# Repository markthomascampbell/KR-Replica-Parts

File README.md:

This repository aims to collect many of the various 3d stencils, Arduino sketches, code, schematics, and any other documentation on creating Knight Rider replica parts.

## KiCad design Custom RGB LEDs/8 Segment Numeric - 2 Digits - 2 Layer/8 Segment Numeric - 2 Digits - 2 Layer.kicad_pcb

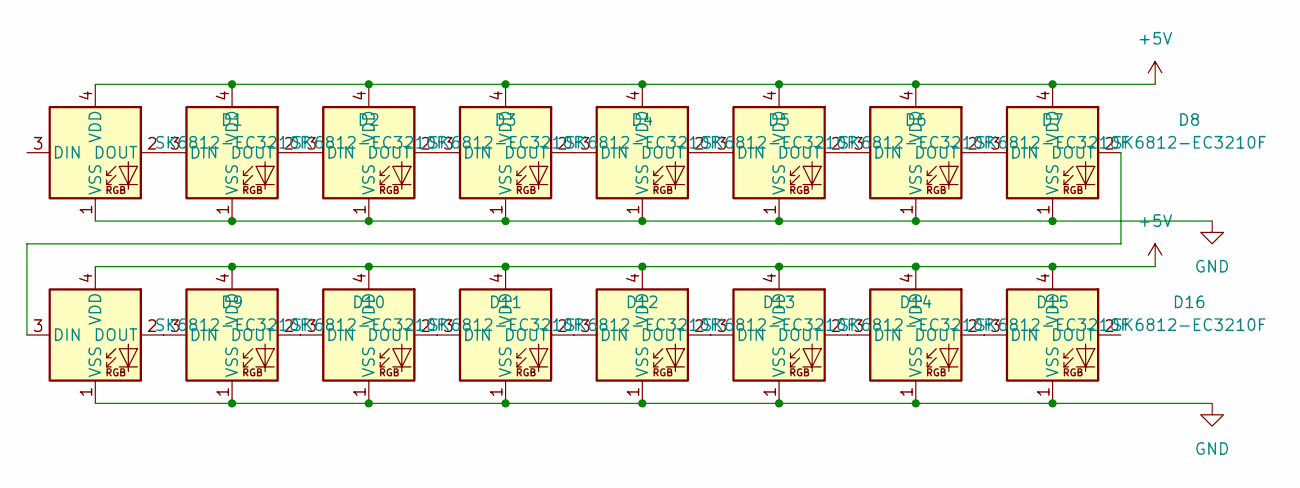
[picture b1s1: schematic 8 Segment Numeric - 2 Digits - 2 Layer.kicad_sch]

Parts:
D1, D2, D3, D4, D5, D6, D7, D8, D9, D10, D11, D12, D13, D14, D15, D16: SK6812-EC3210F

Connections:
+5V: D1.4 (VDD), D2.4 (VDD), D3.4 (VDD), D4.4 (VDD), D5.4 (VDD), D6.4 (VDD), D7.4 (VDD), D8.4 (VDD), D9.4 (VDD), D10.4 (VDD), D11.4 (VDD), D12.4 (VDD), D13.4 (VDD), D14.4 (VDD), D15.4 (VDD), D16.4 (VDD); also elsewhere on the board
GND: D1.1 (VSS), D2.1 (VSS), D3.1 (VSS), D4.1 (VSS), D5.1 (VSS), D6.1 (VSS), D7.1 (VSS), D8.1 (VSS), D9.1 (VSS), D10.1 (VSS), D11.1 (VSS), D12.1 (VSS), D13.1 (VSS), D14.1 (VSS), D15.1 (VSS), D16.1 (VSS); also elsewhere on the board
unnamed: D1.2 (DOUT), D2.3 (DIN)
unnamed: D2.2 (DOUT), D3.3 (DIN)
unnamed: D3.2 (DOUT), D4.3 (DIN)
unnamed: D4.2 (DOUT), D5.3 (DIN)
unnamed: D5.2 (DOUT), D6.3 (DIN)
unnamed: D6.2 (DOUT), D7.3 (DIN)
unnamed: D7.2 (DOUT), D8.3 (DIN)
unnamed: D8.2 (DOUT), D9.3 (DIN)
unnamed: D9.2 (DOUT), D10.3 (DIN)
unnamed: D10.2 (DOUT), D11.3 (DIN)
unnamed: D11.2 (DOUT), D12.3 (DIN)
unnamed: D12.2 (DOUT), D13.3 (DIN)
unnamed: D13.2 (DOUT), D14.3 (DIN)
unnamed: D14.2 (DOUT), D15.3 (DIN)
unnamed: D15.2 (DOUT), D16.3 (DIN)

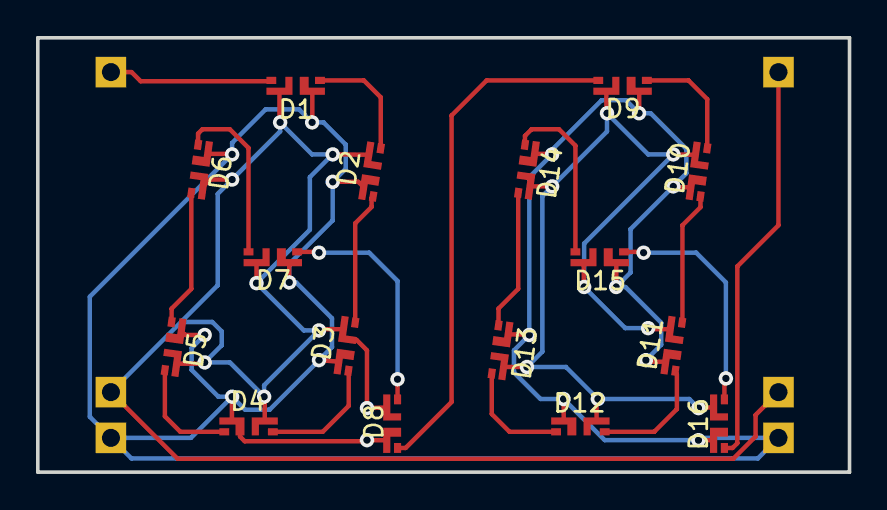
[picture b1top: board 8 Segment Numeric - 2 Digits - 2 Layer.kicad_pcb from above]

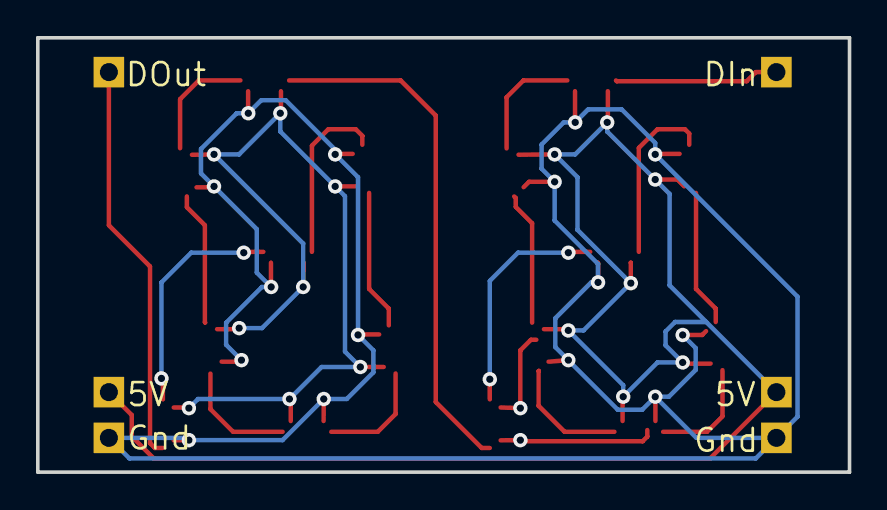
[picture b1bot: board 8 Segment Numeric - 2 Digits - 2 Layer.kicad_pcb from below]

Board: 2 copper layers, 45.1 x 24.1 mm, 18 parts (2 on the bottom side), 17 nets.

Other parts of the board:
5V: (no value)
Gnd: (no value)

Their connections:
+5V: 5V.1; also elsewhere on the board
GND: Gnd.1; also elsewhere on the board

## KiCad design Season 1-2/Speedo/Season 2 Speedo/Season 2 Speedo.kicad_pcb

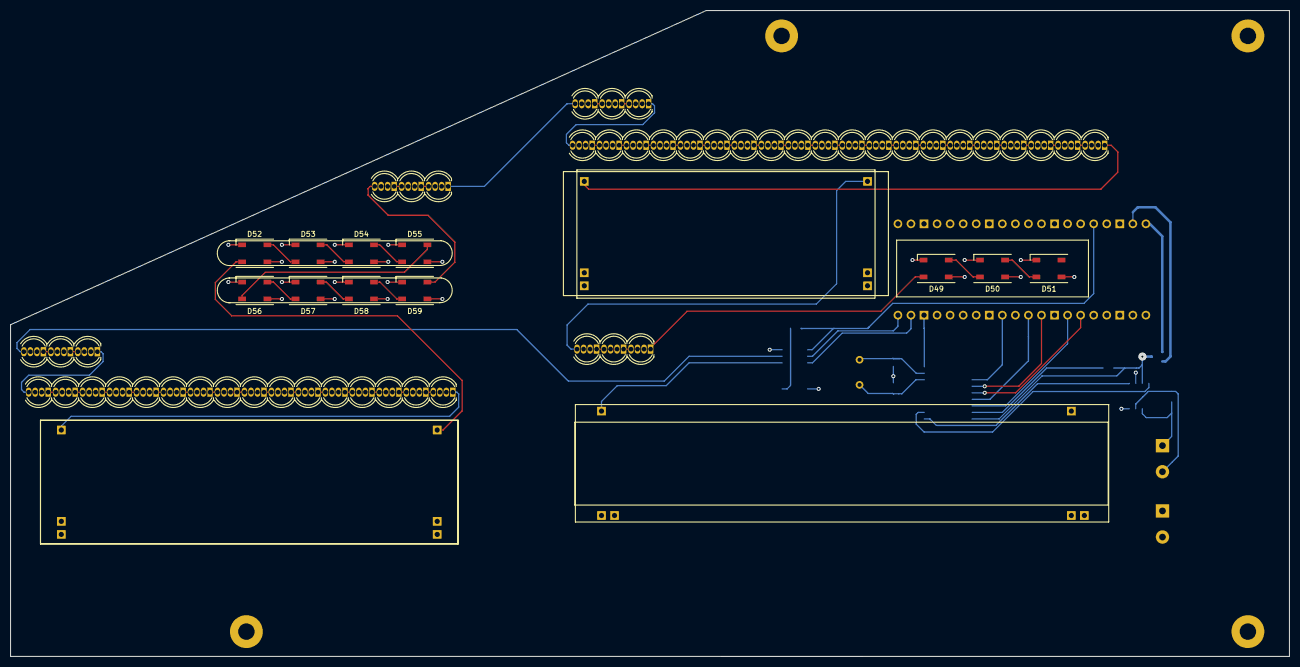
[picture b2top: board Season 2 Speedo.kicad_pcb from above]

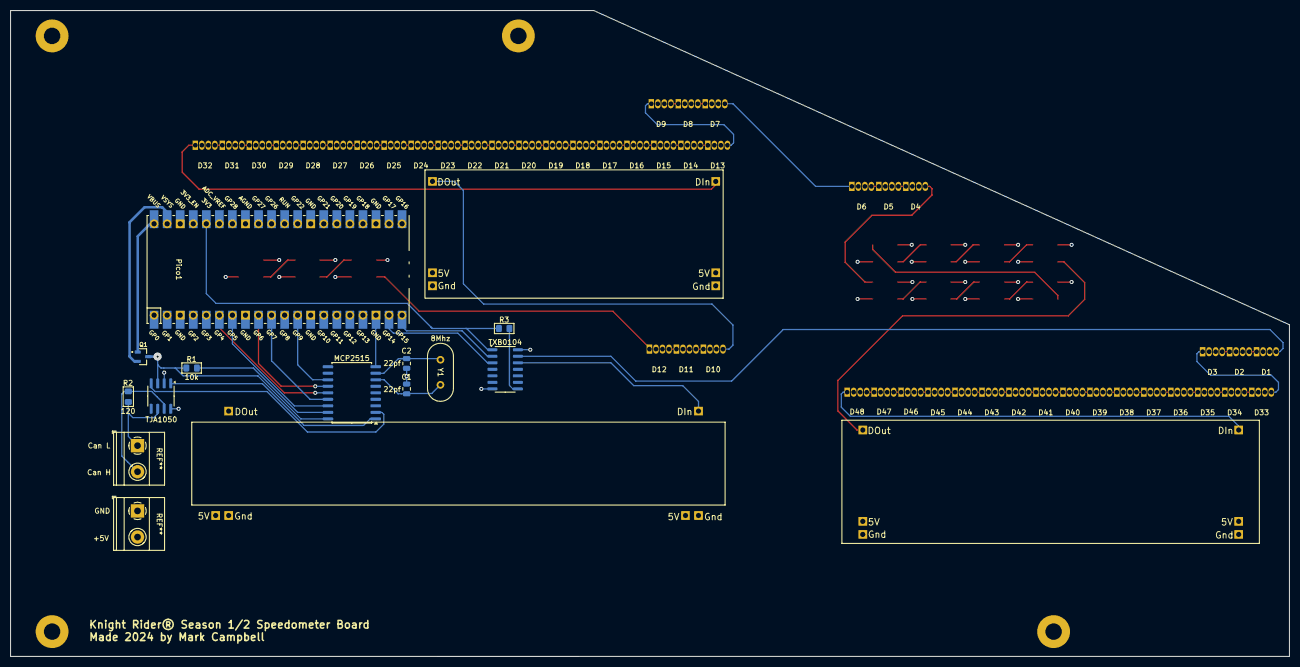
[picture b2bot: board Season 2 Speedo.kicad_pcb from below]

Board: 4 copper layers, 248.9 x 125.7 mm, 74 parts (15 on the bottom side), 77 nets.

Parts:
5V, 5V#2: (no value)
C1, C2: 22pf; C_0805_2012Metric
D1, D2, D3, D4, D5, D6, D7, D8, D9, D10, D11, D12, D13, D14, D15, D16, D17, D18, D19, D20, D21, D22, D23, D24, D25, D26, D27, D28, D29, D30, D31, D32, D33, D34, D35, D36, D37, D38, D39, D40, D41, D42, D43, D44, D45, D46, D47, D48: NeoPixel_THT; LED_D5.0mm-4_RGB_Circular_Margin
D49, D50, D51, D52, D53, D54, D55, D56, D57, D58, D59: WS2812B; LED_WS2812B_PLCC4_5.0x5.0mm_P3.2mm
Gnd: (no value)
Gnd#2: (no value)
MCP2515: MCP2515-xSO; SOIC-18W_7.5x11.6mm_P1.27mm
Pico1: Pico1; RPi_Pico_SMD_TH
Q1: DMG2305UX; SOT91P240X110-3N_DMG2305UX-7
R1, R3: 10k; R_0805_2012Metric_Pad1.15x1.40mm
R2: 120; R_0805_2012Metric_Pad1.15x1.40mm
TJA1050: TJA1051T; SOIC-8_3.9x4.9mm_P1.27mm
TXB0104: TXB0104D; SOIC-14_3.9x8.7mm_P1.27mm
Y1: 8Mhz; Crystal_HC49-U_Vertical

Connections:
+5V: 5V.1, 5V#2.1, D1.3 (VDD), D2.3 (VDD), D3.3 (VDD), D4.3 (VDD), D5.3 (VDD), D6.3 (VDD), D7.3 (VDD), D8.3 (VDD), D9.3 (VDD), D10.3 (VDD), D11.3 (VDD), D12.3 (VDD), D13.3 (VDD), D14.3 (VDD), D15.3 (VDD), D16.3 (VDD), D17.3 (VDD), D18.3 (VDD), D19.3 (VDD), D20.3 (VDD), D21.3 (VDD), D22.3 (VDD), D23.3 (VDD), D24.3 (VDD), D25.3 (VDD), D26.3 (VDD), D27.3 (VDD), D28.3 (VDD), D29.3 (VDD), D30.3 (VDD), D31.3 (VDD), D32.3 (VDD), D33.3 (VDD), D34.3 (VDD), D35.3 (VDD), D36.3 (VDD), D37.3 (VDD), D38.3 (VDD), D39.3 (VDD), D40.3 (VDD), D41.3 (VDD), D42.3 (VDD), D43.3 (VDD), D44.3 (VDD), D45.3 (VDD), D46.3 (VDD), D47.3 (VDD), D48.3 (VDD), D49.1 (VDD), D50.1 (VDD), D51.1 (VDD), D52.1 (VDD), D53.1 (VDD), D54.1 (VDD), D55.1 (VDD), D56.1 (VDD), D57.1 (VDD), D58.1 (VDD), D59.1 (VDD), MCP2515.18 (VDD), Q1.3 (D), R1.1, TJA1050.3 (VCC), TXB0104.14 (VCCB)
GND: C1.1, C2.1, D1.2 (GND), D2.2 (GND), D3.2 (GND), D4.2 (GND), D5.2 (GND), D6.2 (GND), D7.2 (GND), D8.2 (GND), D9.2 (GND), D10.2 (GND), D11.2 (GND), D12.2 (GND), D13.2 (GND), D14.2 (GND), D15.2 (GND), D16.2 (GND), D17.2 (GND), D18.2 (GND), D19.2 (GND), D20.2 (GND), D21.2 (GND), D22.2 (GND), D23.2 (GND), D24.2 (GND), D25.2 (GND), D26.2 (GND), D27.2 (GND), D28.2 (GND), D29.2 (GND), D30.2 (GND), D31.2 (GND), D32.2 (GND), D33.2 (GND), D34.2 (GND), D35.2 (GND), D36.2 (GND), D37.2 (GND), D38.2 (GND), D39.2 (GND), D40.2 (GND), D41.2 (GND), D42.2 (GND), D43.2 (GND), D44.2 (GND), D45.2 (GND), D46.2 (GND), D47.2 (GND), D48.2 (GND), D49.3 (VSS), D50.3 (VSS), D51.3 (VSS), D52.3 (VSS), D53.3 (VSS), D54.3 (VSS), D55.3 (VSS), D56.3 (VSS), D57.3 (VSS), D58.3 (VSS), D59.3 (VSS), Gnd.1, Gnd#2.1, MCP2515.9 (VSS), Pico1.3 (GND), Pico1.8 (GND), Pico1.13 (GND), Pico1.18 (GND), Pico1.23 (GND), Pico1.28 (GND), Pico1.33 (AGND), Pico1.38 (GND), TJA1050.2 (GND), TJA1050.8 (S), TXB0104.7 (GND)
unnamed: D1.4 (DIN), TXB0104.13 (B1)
unnamed: D1.1 (DOUT), D2.4 (DIN)
unnamed: D2.1 (DOUT), D3.4 (DIN)
unnamed: D3.1 (DOUT), D33.4 (DIN)
unnamed: D4.4 (DIN), D59.2 (DOUT)
unnamed: D4.1 (DOUT), D5.4 (DIN)
unnamed: D5.1 (DOUT), D6.4 (DIN)
unnamed: D6.1 (DOUT), D7.4 (DIN)
unnamed: D7.1 (DOUT), D8.4 (DIN)
unnamed: D8.1 (DOUT), D9.4 (DIN)
unnamed: D10.1 (DOUT), D11.4 (DIN)
unnamed: D11.1 (DOUT), D12.4 (DIN)
unnamed: D12.1 (DOUT), D49.4 (DIN)
unnamed: D9.1 (DOUT), D13.4 (DIN)
unnamed: D13.1 (DOUT), D14.4 (DIN)
unnamed: D14.1 (DOUT), D15.4 (DIN)
unnamed: D15.1 (DOUT), D16.4 (DIN)
unnamed: D16.1 (DOUT), D17.4 (DIN)
unnamed: D17.1 (DOUT), D18.4 (DIN)
unnamed: D18.1 (DOUT), D19.4 (DIN)
unnamed: D19.1 (DOUT), D20.4 (DIN)
unnamed: D20.1 (DOUT), D21.4 (DIN)
unnamed: D21.1 (DOUT), D22.4 (DIN)
unnamed: D22.1 (DOUT), D23.4 (DIN)
unnamed: D23.1 (DOUT), D24.4 (DIN)
unnamed: D24.1 (DOUT), D25.4 (DIN)
unnamed: D25.1 (DOUT), D26.4 (DIN)
unnamed: D26.1 (DOUT), D27.4 (DIN)
unnamed: D27.1 (DOUT), D28.4 (DIN)
unnamed: D28.1 (DOUT), D29.4 (DIN)
unnamed: D29.1 (DOUT), D30.4 (DIN)
unnamed: D30.1 (DOUT), D31.4 (DIN)
unnamed: D31.1 (DOUT), D32.4 (DIN)
unnamed: D33.1 (DOUT), D34.4 (DIN)
unnamed: D34.1 (DOUT), D35.4 (DIN)
unnamed: D35.1 (DOUT), D36.4 (DIN)
unnamed: D36.1 (DOUT), D37.4 (DIN)
unnamed: D37.1 (DOUT), D38.4 (DIN)
unnamed: D38.1 (DOUT), D39.4 (DIN)
unnamed: D39.1 (DOUT), D40.4 (DIN)
unnamed: D40.1 (DOUT), D41.4 (DIN)
unnamed: D41.1 (DOUT), D42.4 (DIN)
unnamed: D42.1 (DOUT), D43.4 (DIN)
unnamed: D43.1 (DOUT), D44.4 (DIN)
unnamed: D44.1 (DOUT), D45.4 (DIN)
unnamed: D45.1 (DOUT), D46.4 (DIN)
unnamed: D46.1 (DOUT), D47.4 (DIN)
unnamed: D47.1 (DOUT), D48.4 (DIN)
unnamed: D49.2 (DOUT), D50.4 (DIN)
unnamed: D50.2 (DOUT), D51.4 (DIN)
unnamed: D52.2 (DOUT), D53.4 (DIN)
unnamed: D53.2 (DOUT), D54.4 (DIN)
unnamed: D54.2 (DOUT), D55.4 (DIN)
unnamed: D55.2 (DOUT), D56.4 (DIN)
unnamed: D56.2 (DOUT), D57.4 (DIN)
unnamed: D57.2 (DOUT), D58.4 (DIN)
unnamed: D58.2 (DOUT), D59.4 (DIN)
unnamed: C2.2, MCP2515.8 (OSC1), Y1.1
unnamed: C1.2, MCP2515.7 (OSC2), Y1.2
unnamed: MCP2515.2 (RXCAN), TJA1050.4 (RXD)
unnamed: MCP2515.13 (SCK), Pico1.9 (GPIO6)
unnamed: MCP2515.14 (SI), Pico1.6 (GPIO4)
unnamed: MCP2515.15 (SO), Pico1.10 (GPIO7)
unnamed: MCP2515.1 (TXCAN), TJA1050.1 (TXD)
unnamed: MCP2515.16 (~CS), Pico1.7 (GPIO5)
unnamed: MCP2515.12 (~INT), Pico1.12 (GPIO9)
unnamed: MCP2515.17 (~RESET), R1.2
unnamed: Pico1.36 (3V3), R3.1, TXB0104.1 (VCCA)
unnamed: Pico1.19 (GPIO14), TXB0104.3 (A2)
unnamed: Pico1.20 (GPIO15), TXB0104.2 (A1)
unnamed: Pico1.40 (VBUS), Q1.1 (G)
unnamed: Pico1.39 (VSYS), Q1.2 (S)
unnamed: R2.2, TJA1050.7 (CANH)
unnamed: R2.1, TJA1050.6 (CANL)
unnamed: R3.2, TXB0104.8 (OE)

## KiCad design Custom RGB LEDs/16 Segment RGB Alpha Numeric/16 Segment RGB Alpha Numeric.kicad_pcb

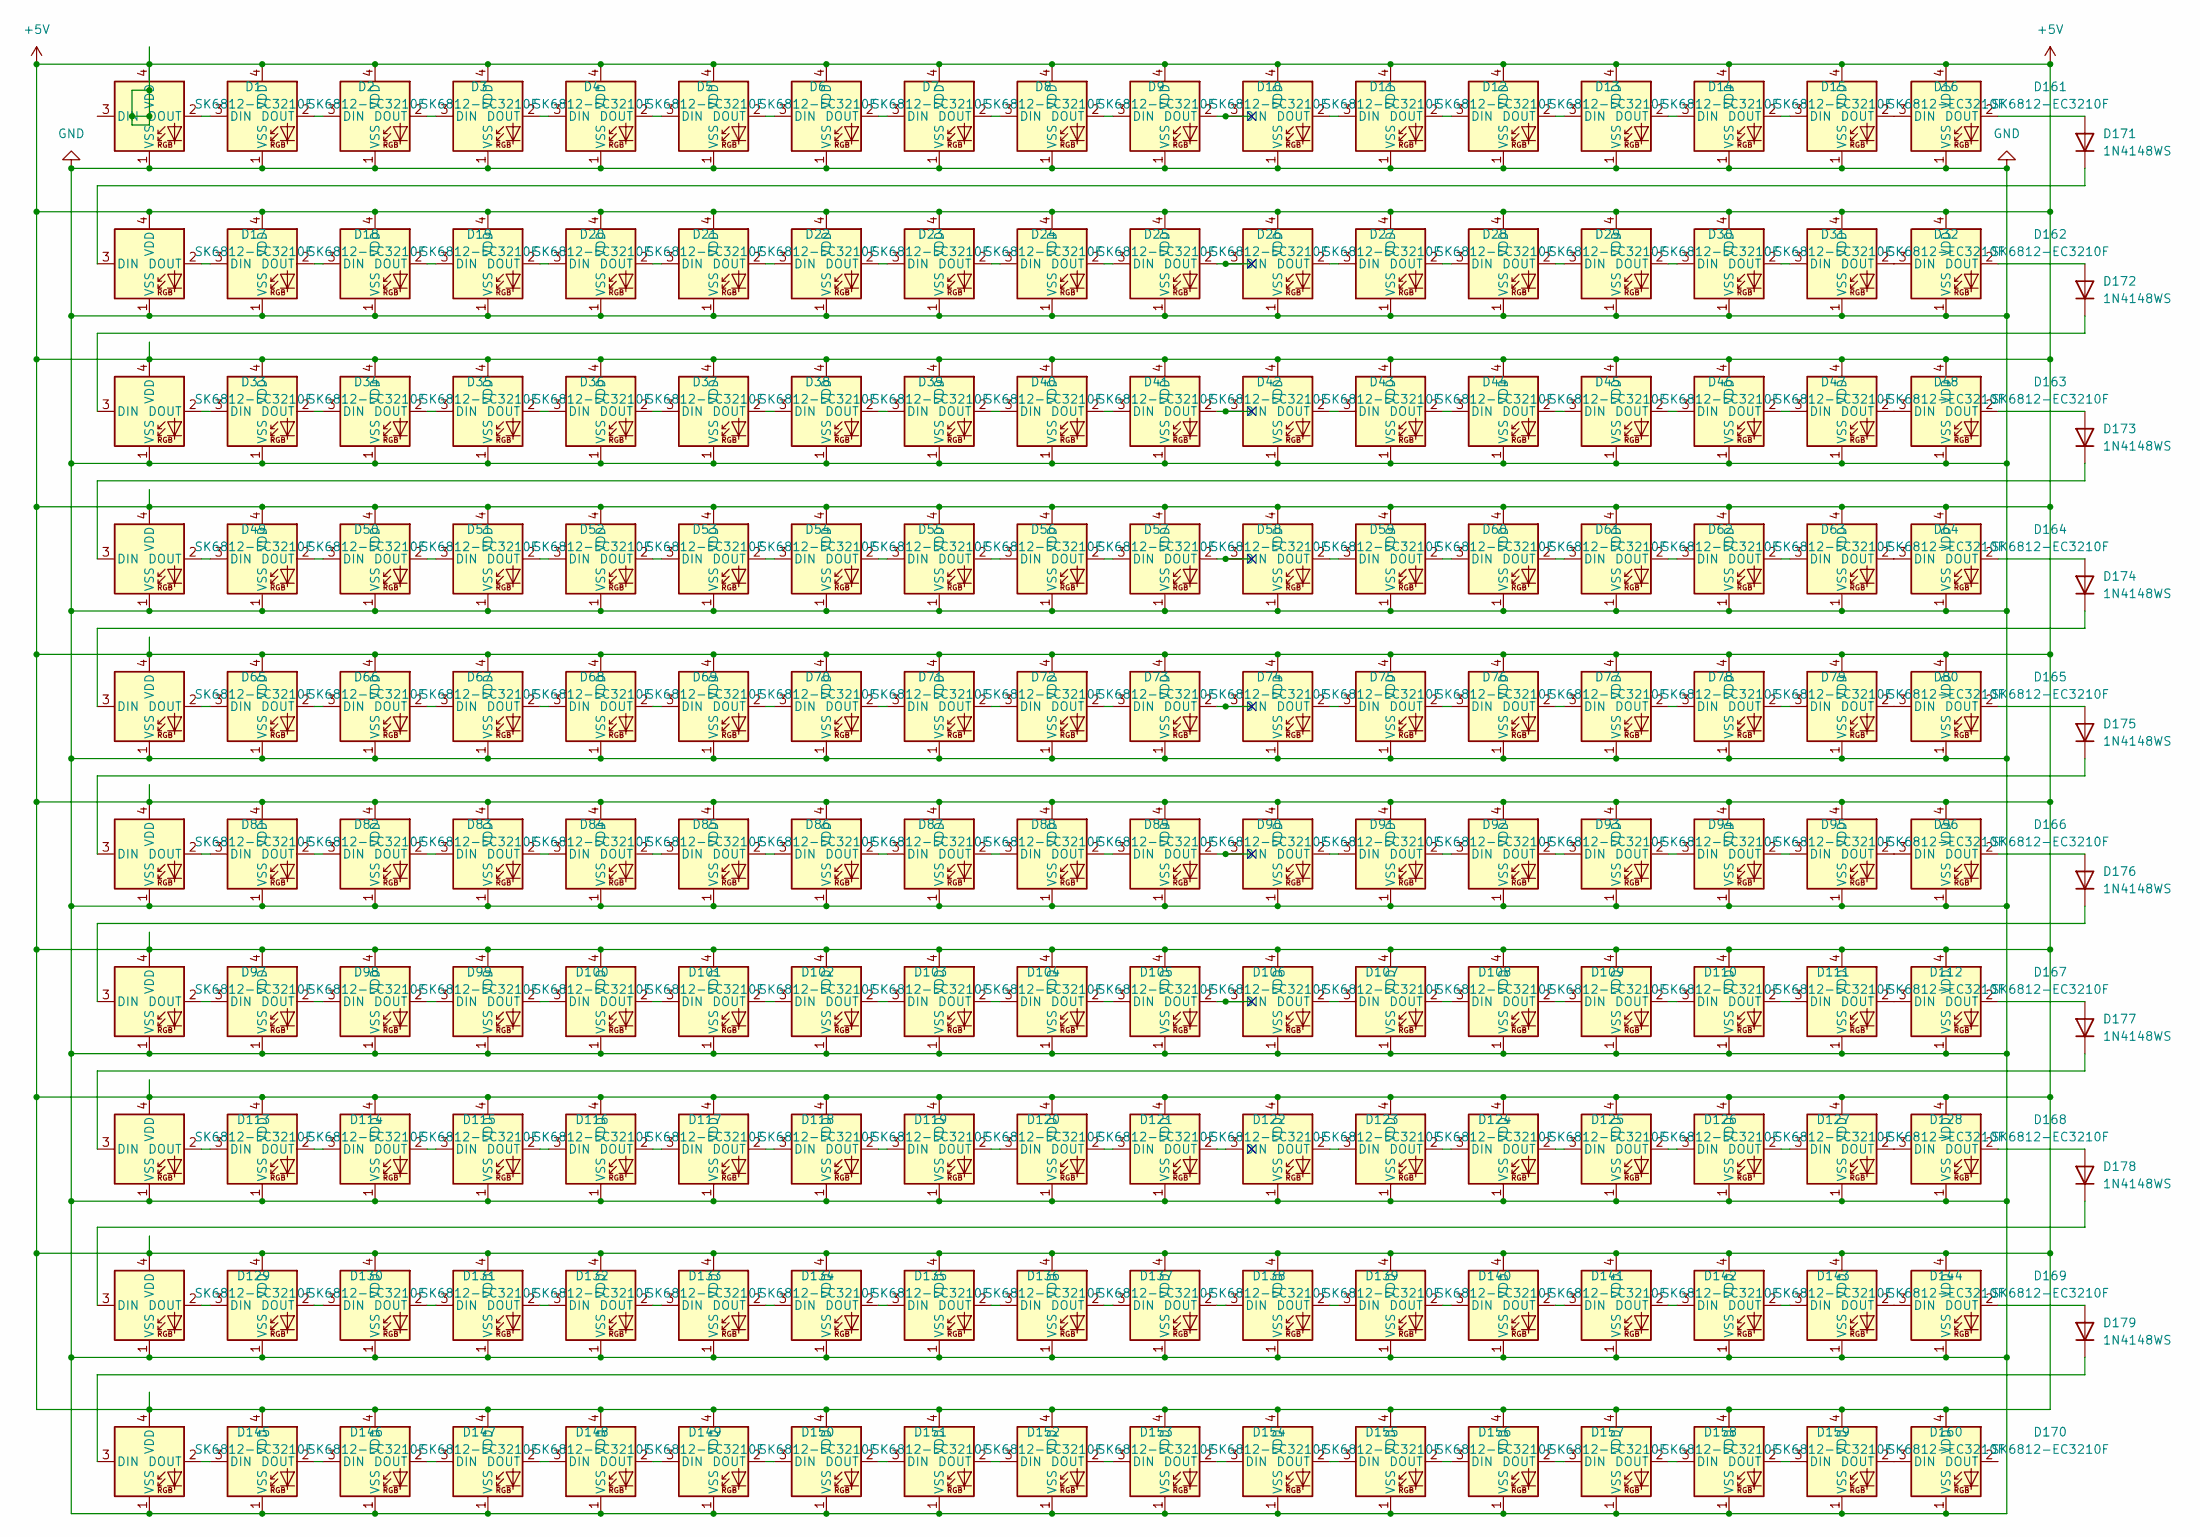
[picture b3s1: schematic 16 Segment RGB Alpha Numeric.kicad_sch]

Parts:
D1, D2, D3, D4, D5, D6, D7, D8, D9, D10, D11, D12, D13, D14, D15, D16, D17, D18, D19, D20, D21, D22, D23, D24, D25, D26, D27, D28, D29, D30, D31, D32, D33, D34, D35, D36, D37, D38, D39, D40, D41, D42, D43, D44, D45, D46, D47, D48, D49, D50, D51, D52, D53, D54, D55, D56, D57, D58, D59, D60, D61, D62, D63, D64, D65, D66, D67, D68, D69, D70, D71, D72, D73, D74, D75, D76, D77, D78, D79, D80, D81, D82, D83, D84, D85, D86, D87, D88, D89, D90, D91, D92, D93, D94, D95, D96, D97, D98, D99, D100, D101, D102, D103, D104, D105, D106, D107, D108, D109, D110, D111, D112, D113, D114, D115, D116, D117, D118, D119, D120, D121, D122, D123, D124, D125, D126, D127, D128, D129, D130, D131, D132, D133, D134, D135, D136, D137, D138, D139, D140, D141, D142, D143, D144, D145, D146, D147, D148, D149, D150, D151, D152, D153, D154, D155, D156, D157, D158, D159, D160, D161, D162, D163, D164, D165, D166, D167, D168, D169, D170: SK6812-EC3210F
D171, D172, D173, D174, D175, D176, D177, D178, D179: 1N4148WS; D_SOD-323

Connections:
+5V: D1.4 (VDD), D2.4 (VDD), D3.4 (VDD), D4.4 (VDD), D5.4 (VDD), D6.4 (VDD), D7.4 (VDD), D8.4 (VDD), D9.4 (VDD), D10.4 (VDD), D11.4 (VDD), D12.4 (VDD), D13.4 (VDD), D14.4 (VDD), D15.4 (VDD), D16.4 (VDD), D17.4 (VDD), D18.4 (VDD), D19.4 (VDD), D20.4 (VDD), D21.4 (VDD), D22.4 (VDD), D23.4 (VDD), D24.4 (VDD), D25.4 (VDD), D26.4 (VDD), D27.4 (VDD), D28.4 (VDD), D29.4 (VDD), D30.4 (VDD), D31.4 (VDD), D32.4 (VDD), D33.4 (VDD), D34.4 (VDD), D35.4 (VDD), D36.4 (VDD), D37.4 (VDD), D38.4 (VDD), D39.4 (VDD), D40.4 (VDD), D41.4 (VDD), D42.4 (VDD), D43.4 (VDD), D44.4 (VDD), D45.4 (VDD), D46.4 (VDD), D47.4 (VDD), D48.4 (VDD), D49.4 (VDD), D50.4 (VDD), D51.4 (VDD), D52.4 (VDD), D53.4 (VDD), D54.4 (VDD), D55.4 (VDD), D56.4 (VDD), D57.4 (VDD), D58.4 (VDD), D59.4 (VDD), D60.4 (VDD), D61.4 (VDD), D62.4 (VDD), D63.4 (VDD), D64.4 (VDD), D65.4 (VDD), D66.4 (VDD), D67.4 (VDD), D68.4 (VDD), D69.4 (VDD), D70.4 (VDD), D71.4 (VDD), D72.4 (VDD), D73.4 (VDD), D74.4 (VDD), D75.4 (VDD), D76.4 (VDD), D77.4 (VDD), D78.4 (VDD), D79.4 (VDD), D80.4 (VDD), D81.4 (VDD), D82.4 (VDD), D83.4 (VDD), D84.4 (VDD), D85.4 (VDD), D86.4 (VDD), D87.4 (VDD), D88.4 (VDD), D89.4 (VDD), D90.4 (VDD), D91.4 (VDD), D92.4 (VDD), D93.4 (VDD), D94.4 (VDD), D95.4 (VDD), D96.4 (VDD), D97.4 (VDD), D98.4 (VDD), D99.4 (VDD), D100.4 (VDD), D101.4 (VDD), D102.4 (VDD), D103.4 (VDD), D104.4 (VDD), D105.4 (VDD), D106.4 (VDD), D107.4 (VDD), D108.4 (VDD), D109.4 (VDD), D110.4 (VDD), D111.4 (VDD), D112.4 (VDD), D113.4 (VDD), D114.4 (VDD), D115.4 (VDD), D116.4 (VDD), D117.4 (VDD), D118.4 (VDD), D119.4 (VDD), D120.4 (VDD), D121.4 (VDD), D122.4 (VDD), D123.4 (VDD), D124.4 (VDD), D125.4 (VDD), D126.4 (VDD), D127.4 (VDD), D128.4 (VDD), D129.4 (VDD), D130.4 (VDD), D131.4 (VDD), D132.4 (VDD), D133.4 (VDD), D134.4 (VDD), D135.4 (VDD), D136.4 (VDD), D137.4 (VDD), D138.4 (VDD), D139.4 (VDD), D140.4 (VDD), D141.4 (VDD), D142.4 (VDD), D143.4 (VDD), D144.4 (VDD), D145.4 (VDD), D146.4 (VDD), D147.4 (VDD), D148.4 (VDD), D149.4 (VDD), D150.4 (VDD), D151.4 (VDD), D152.4 (VDD), D153.4 (VDD), D154.4 (VDD), D155.4 (VDD), D156.4 (VDD), D157.4 (VDD), D158.4 (VDD), D159.4 (VDD), D160.4 (VDD), D161.4 (VDD), D162.4 (VDD), D163.4 (VDD), D164.4 (VDD), D165.4 (VDD), D166.4 (VDD), D167.4 (VDD), D168.4 (VDD), D169.4 (VDD), D170.4 (VDD)
GND: D1.1 (VSS), D2.1 (VSS), D3.1 (VSS), D4.1 (VSS), D5.1 (VSS), D6.1 (VSS), D7.1 (VSS), D8.1 (VSS), D9.1 (VSS), D10.1 (VSS), D11.1 (VSS), D12.1 (VSS), D13.1 (VSS), D14.1 (VSS), D15.1 (VSS), D16.1 (VSS), D17.1 (VSS), D18.1 (VSS), D19.1 (VSS), D20.1 (VSS), D21.1 (VSS), D22.1 (VSS), D23.1 (VSS), D24.1 (VSS), D25.1 (VSS), D26.1 (VSS), D27.1 (VSS), D28.1 (VSS), D29.1 (VSS), D30.1 (VSS), D31.1 (VSS), D32.1 (VSS), D33.1 (VSS), D34.1 (VSS), D35.1 (VSS), D36.1 (VSS), D37.1 (VSS), D38.1 (VSS), D39.1 (VSS), D40.1 (VSS), D41.1 (VSS), D42.1 (VSS), D43.1 (VSS), D44.1 (VSS), D45.1 (VSS), D46.1 (VSS), D47.1 (VSS), D48.1 (VSS), D49.1 (VSS), D50.1 (VSS), D51.1 (VSS), D52.1 (VSS), D53.1 (VSS), D54.1 (VSS), D55.1 (VSS), D56.1 (VSS), D57.1 (VSS), D58.1 (VSS), D59.1 (VSS), D60.1 (VSS), D61.1 (VSS), D62.1 (VSS), D63.1 (VSS), D64.1 (VSS), D65.1 (VSS), D66.1 (VSS), D67.1 (VSS), D68.1 (VSS), D69.1 (VSS), D70.1 (VSS), D71.1 (VSS), D72.1 (VSS), D73.1 (VSS), D74.1 (VSS), D75.1 (VSS), D76.1 (VSS), D77.1 (VSS), D78.1 (VSS), D79.1 (VSS), D80.1 (VSS), D81.1 (VSS), D82.1 (VSS), D83.1 (VSS), D84.1 (VSS), D85.1 (VSS), D86.1 (VSS), D87.1 (VSS), D88.1 (VSS), D89.1 (VSS), D90.1 (VSS), D91.1 (VSS), D92.1 (VSS), D93.1 (VSS), D94.1 (VSS), D95.1 (VSS), D96.1 (VSS), D97.1 (VSS), D98.1 (VSS), D99.1 (VSS), D100.1 (VSS), D101.1 (VSS), D102.1 (VSS), D103.1 (VSS), D104.1 (VSS), D105.1 (VSS), D106.1 (VSS), D107.1 (VSS), D108.1 (VSS), D109.1 (VSS), D110.1 (VSS), D111.1 (VSS), D112.1 (VSS), D113.1 (VSS), D114.1 (VSS), D115.1 (VSS), D116.1 (VSS), D117.1 (VSS), D118.1 (VSS), D119.1 (VSS), D120.1 (VSS), D121.1 (VSS), D122.1 (VSS), D123.1 (VSS), D124.1 (VSS), D125.1 (VSS), D126.1 (VSS), D127.1 (VSS), D128.1 (VSS), D129.1 (VSS), D130.1 (VSS), D131.1 (VSS), D132.1 (VSS), D133.1 (VSS), D134.1 (VSS), D135.1 (VSS), D136.1 (VSS), D137.1 (VSS), D138.1 (VSS), D139.1 (VSS), D140.1 (VSS), D141.1 (VSS), D142.1 (VSS), D143.1 (VSS), D144.1 (VSS), D145.1 (VSS), D146.1 (VSS), D147.1 (VSS), D148.1 (VSS), D149.1 (VSS), D150.1 (VSS), D151.1 (VSS), D152.1 (VSS), D153.1 (VSS), D154.1 (VSS), D155.1 (VSS), D156.1 (VSS), D157.1 (VSS), D158.1 (VSS), D159.1 (VSS), D160.1 (VSS), D161.1 (VSS), D162.1 (VSS), D163.1 (VSS), D164.1 (VSS), D165.1 (VSS), D166.1 (VSS), D167.1 (VSS), D168.1 (VSS), D169.1 (VSS), D170.1 (VSS)
unnamed: D1.2 (DOUT), D2.3 (DIN)
unnamed: D2.2 (DOUT), D3.3 (DIN)
unnamed: D3.2 (DOUT), D4.3 (DIN)
unnamed: D4.2 (DOUT), D5.3 (DIN)
unnamed: D5.2 (DOUT), D6.3 (DIN)
unnamed: D6.2 (DOUT), D7.3 (DIN)
unnamed: D7.2 (DOUT), D8.3 (DIN)
unnamed: D8.2 (DOUT), D9.3 (DIN)
unnamed: D9.2 (DOUT), D10.3 (DIN)
unnamed: D11.2 (DOUT), D12.3 (DIN)
unnamed: D12.2 (DOUT), D13.3 (DIN)
unnamed: D13.2 (DOUT), D14.3 (DIN)
unnamed: D14.2 (DOUT), D15.3 (DIN)
unnamed: D15.2 (DOUT), D16.3 (DIN)
unnamed: D16.2 (DOUT), D161.3 (DIN)
unnamed: D17.3 (DIN), D171.1 (K)
unnamed: D17.2 (DOUT), D18.3 (DIN)
unnamed: D18.2 (DOUT), D19.3 (DIN)
unnamed: D19.2 (DOUT), D20.3 (DIN)
unnamed: D20.2 (DOUT), D21.3 (DIN)
unnamed: D21.2 (DOUT), D22.3 (DIN)
unnamed: D22.2 (DOUT), D23.3 (DIN)
unnamed: D23.2 (DOUT), D24.3 (DIN)
unnamed: D24.2 (DOUT), D25.3 (DIN)
unnamed: D25.2 (DOUT), D26.3 (DIN)
unnamed: D27.2 (DOUT), D28.3 (DIN)
unnamed: D28.2 (DOUT), D29.3 (DIN)
unnamed: D29.2 (DOUT), D30.3 (DIN)
unnamed: D30.2 (DOUT), D31.3 (DIN)
unnamed: D31.2 (DOUT), D32.3 (DIN)
unnamed: D33.2 (DOUT), D34.3 (DIN)
unnamed: D34.2 (DOUT), D35.3 (DIN)
unnamed: D35.2 (DOUT), D36.3 (DIN)
unnamed: D36.2 (DOUT), D37.3 (DIN)
unnamed: D37.2 (DOUT), D38.3 (DIN)
unnamed: D38.2 (DOUT), D39.3 (DIN)
unnamed: D39.2 (DOUT), D40.3 (DIN)
unnamed: D40.2 (DOUT), D41.3 (DIN)
unnamed: D41.2 (DOUT), D42.3 (DIN)
unnamed: D43.2 (DOUT), D44.3 (DIN)
unnamed: D44.2 (DOUT), D45.3 (DIN)
unnamed: D45.2 (DOUT), D46.3 (DIN)
unnamed: D46.2 (DOUT), D47.3 (DIN)
unnamed: D47.2 (DOUT), D48.3 (DIN)
unnamed: D49.2 (DOUT), D50.3 (DIN)
unnamed: D50.2 (DOUT), D51.3 (DIN)
unnamed: D51.2 (DOUT), D52.3 (DIN)
unnamed: D52.2 (DOUT), D53.3 (DIN)
unnamed: D53.2 (DOUT), D54.3 (DIN)
unnamed: D54.2 (DOUT), D55.3 (DIN)
unnamed: D55.2 (DOUT), D56.3 (DIN)
unnamed: D56.2 (DOUT), D57.3 (DIN)
unnamed: D57.2 (DOUT), D58.3 (DIN)
unnamed: D59.2 (DOUT), D60.3 (DIN)
unnamed: D60.2 (DOUT), D61.3 (DIN)
unnamed: D61.2 (DOUT), D62.3 (DIN)
unnamed: D62.2 (DOUT), D63.3 (DIN)
unnamed: D63.2 (DOUT), D64.3 (DIN)
unnamed: D65.2 (DOUT), D66.3 (DIN)
unnamed: D66.2 (DOUT), D67.3 (DIN)
unnamed: D67.2 (DOUT), D68.3 (DIN)
unnamed: D68.2 (DOUT), D69.3 (DIN)
unnamed: D69.2 (DOUT), D70.3 (DIN)
unnamed: D70.2 (DOUT), D71.3 (DIN)
unnamed: D71.2 (DOUT), D72.3 (DIN)
unnamed: D72.2 (DOUT), D73.3 (DIN)
unnamed: D73.2 (DOUT), D74.3 (DIN)
unnamed: D75.2 (DOUT), D76.3 (DIN)
unnamed: D76.2 (DOUT), D77.3 (DIN)
unnamed: D77.2 (DOUT), D78.3 (DIN)
unnamed: D78.2 (DOUT), D79.3 (DIN)
unnamed: D79.2 (DOUT), D80.3 (DIN)
unnamed: D81.2 (DOUT), D82.3 (DIN)
unnamed: D82.2 (DOUT), D83.3 (DIN)
unnamed: D83.2 (DOUT), D84.3 (DIN)
unnamed: D84.2 (DOUT), D85.3 (DIN)
unnamed: D85.2 (DOUT), D86.3 (DIN)
unnamed: D86.2 (DOUT), D87.3 (DIN)
unnamed: D87.2 (DOUT), D88.3 (DIN)
unnamed: D88.2 (DOUT), D89.3 (DIN)
unnamed: D89.2 (DOUT), D90.3 (DIN)
unnamed: D91.2 (DOUT), D92.3 (DIN)
unnamed: D92.2 (DOUT), D93.3 (DIN)
unnamed: D93.2 (DOUT), D94.3 (DIN)
unnamed: D94.2 (DOUT), D95.3 (DIN)
unnamed: D95.2 (DOUT), D96.3 (DIN)
unnamed: D97.2 (DOUT), D98.3 (DIN)
unnamed: D98.2 (DOUT), D99.3 (DIN)
unnamed: D99.2 (DOUT), D100.3 (DIN)
unnamed: D100.2 (DOUT), D101.3 (DIN)
unnamed: D101.2 (DOUT), D102.3 (DIN)
unnamed: D102.2 (DOUT), D103.3 (DIN)
unnamed: D103.2 (DOUT), D104.3 (DIN)
unnamed: D104.2 (DOUT), D105.3 (DIN)
unnamed: D105.2 (DOUT), D106.3 (DIN)
unnamed: D107.2 (DOUT), D108.3 (DIN)
unnamed: D108.2 (DOUT), D109.3 (DIN)
unnamed: D109.2 (DOUT), D110.3 (DIN)
unnamed: D110.2 (DOUT), D111.3 (DIN)
unnamed: D111.2 (DOUT), D112.3 (DIN)
unnamed: D112.2 (DOUT), D167.3 (DIN)
unnamed: D113.3 (DIN), D177.1 (K)
unnamed: D113.2 (DOUT), D114.3 (DIN)
unnamed: D114.2 (DOUT), D115.3 (DIN)
unnamed: D115.2 (DOUT), D116.3 (DIN)
unnamed: D116.2 (DOUT), D117.3 (DIN)
unnamed: D117.2 (DOUT), D118.3 (DIN)
unnamed: D118.2 (DOUT), D119.3 (DIN)
unnamed: D119.2 (DOUT), D120.3 (DIN)
unnamed: D120.2 (DOUT), D121.3 (DIN)
unnamed: D121.2 (DOUT), D122.3 (DIN)
unnamed: D122.2 (DOUT), D123.3 (DIN)
unnamed: D123.2 (DOUT), D124.3 (DIN)
unnamed: D124.2 (DOUT), D125.3 (DIN)
unnamed: D125.2 (DOUT), D126.3 (DIN)
unnamed: D126.2 (DOUT), D127.3 (DIN)
unnamed: D127.2 (DOUT), D128.3 (DIN)
unnamed: D128.2 (DOUT), D168.3 (DIN)
unnamed: D129.3 (DIN), D178.1 (K)
unnamed: D129.2 (DOUT), D130.3 (DIN)
unnamed: D130.2 (DOUT), D131.3 (DIN)
unnamed: D131.2 (DOUT), D132.3 (DIN)
unnamed: D132.2 (DOUT), D133.3 (DIN)
unnamed: D133.2 (DOUT), D134.3 (DIN)
unnamed: D134.2 (DOUT), D135.3 (DIN)
unnamed: D135.2 (DOUT), D136.3 (DIN)
unnamed: D136.2 (DOUT), D137.3 (DIN)
unnamed: D137.2 (DOUT), D138.3 (DIN)
unnamed: D138.2 (DOUT), D139.3 (DIN)
unnamed: D139.2 (DOUT), D140.3 (DIN)
unnamed: D140.2 (DOUT), D141.3 (DIN)
unnamed: D141.2 (DOUT), D142.3 (DIN)
unnamed: D142.2 (DOUT), D143.3 (DIN)
unnamed: D143.2 (DOUT), D144.3 (DIN)
unnamed: D144.2 (DOUT), D169.3 (DIN)
unnamed: D145.3 (DIN), D179.1 (K)
unnamed: D145.2 (DOUT), D146.3 (DIN)
unnamed: D146.2 (DOUT), D147.3 (DIN)
unnamed: D147.2 (DOUT), D148.3 (DIN)
unnamed: D148.2 (DOUT), D149.3 (DIN)
unnamed: D149.2 (DOUT), D150.3 (DIN)
unnamed: D150.2 (DOUT), D151.3 (DIN)
unnamed: D151.2 (DOUT), D152.3 (DIN)
unnamed: D152.2 (DOUT), D153.3 (DIN)
unnamed: D153.2 (DOUT), D154.3 (DIN)
unnamed: D154.2 (DOUT), D155.3 (DIN)
unnamed: D155.2 (DOUT), D156.3 (DIN)
unnamed: D156.2 (DOUT), D157.3 (DIN)
unnamed: D157.2 (DOUT), D158.3 (DIN)
unnamed: D158.2 (DOUT), D159.3 (DIN)
unnamed: D159.2 (DOUT), D160.3 (DIN)
unnamed: D160.2 (DOUT), D170.3 (DIN)
unnamed: D161.2 (DOUT), D171.2 (A)
unnamed: D32.2 (DOUT), D162.3 (DIN)
unnamed: D162.2 (DOUT), D172.2 (A)
unnamed: D48.2 (DOUT), D163.3 (DIN)
unnamed: D163.2 (DOUT), D173.2 (A)
unnamed: D64.2 (DOUT), D164.3 (DIN)
unnamed: D164.2 (DOUT), D174.2 (A)
unnamed: D80.2 (DOUT), D165.3 (DIN)
unnamed: D165.2 (DOUT), D175.2 (A)
unnamed: D96.2 (DOUT), D166.3 (DIN)
unnamed: D166.2 (DOUT), D176.2 (A)
unnamed: D167.2 (DOUT), D177.2 (A)
unnamed: D168.2 (DOUT), D178.2 (A)
unnamed: D169.2 (DOUT), D179.2 (A)
unnamed: D33.3 (DIN), D172.1 (K)
unnamed: D49.3 (DIN), D173.1 (K)
unnamed: D65.3 (DIN), D174.1 (K)
unnamed: D81.3 (DIN), D175.1 (K)
unnamed: D97.3 (DIN), D176.1 (K)

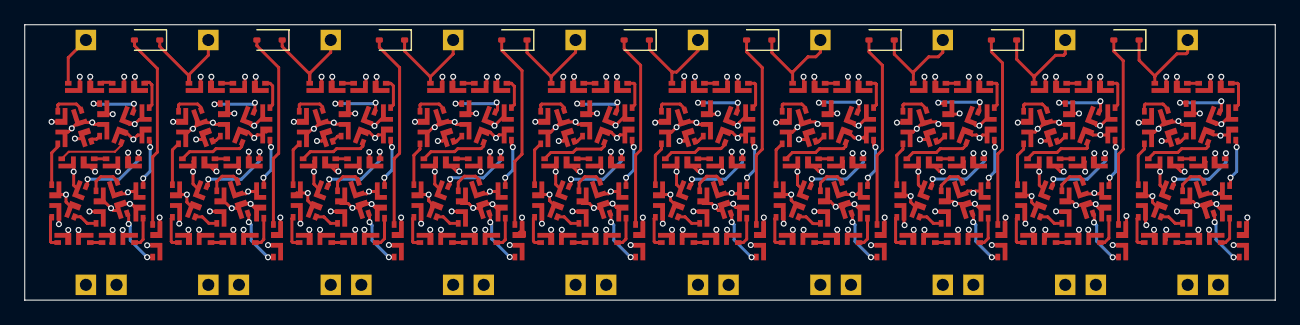
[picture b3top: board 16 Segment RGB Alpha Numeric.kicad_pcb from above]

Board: 4 copper layers, 103.8 x 22.9 mm, 179 parts (0 on the bottom side), 173 nets.

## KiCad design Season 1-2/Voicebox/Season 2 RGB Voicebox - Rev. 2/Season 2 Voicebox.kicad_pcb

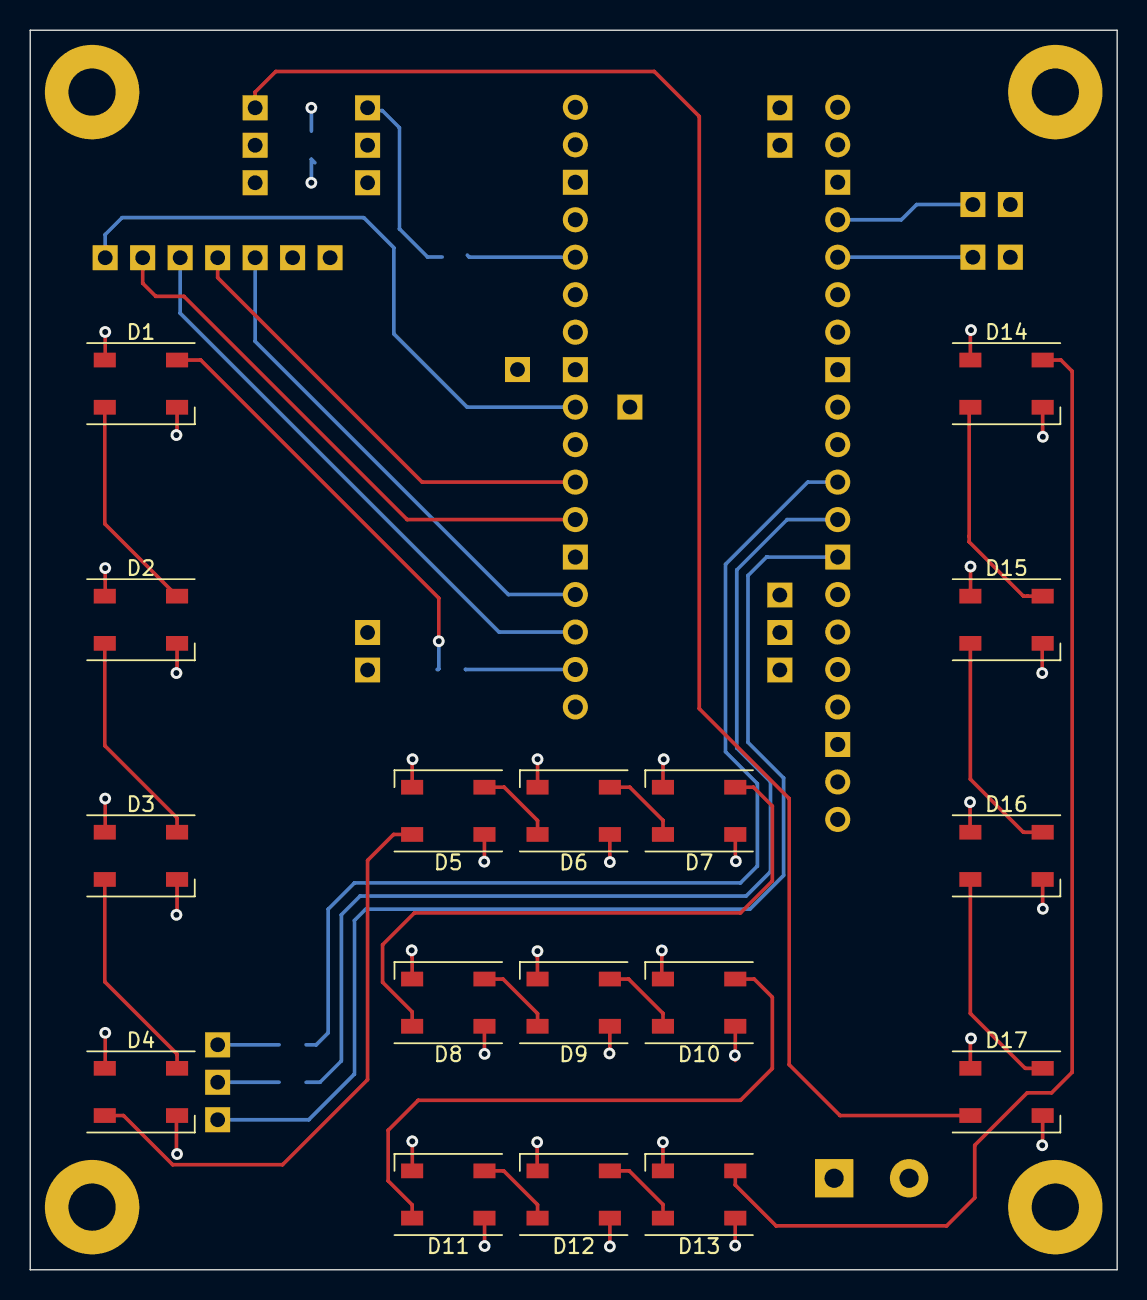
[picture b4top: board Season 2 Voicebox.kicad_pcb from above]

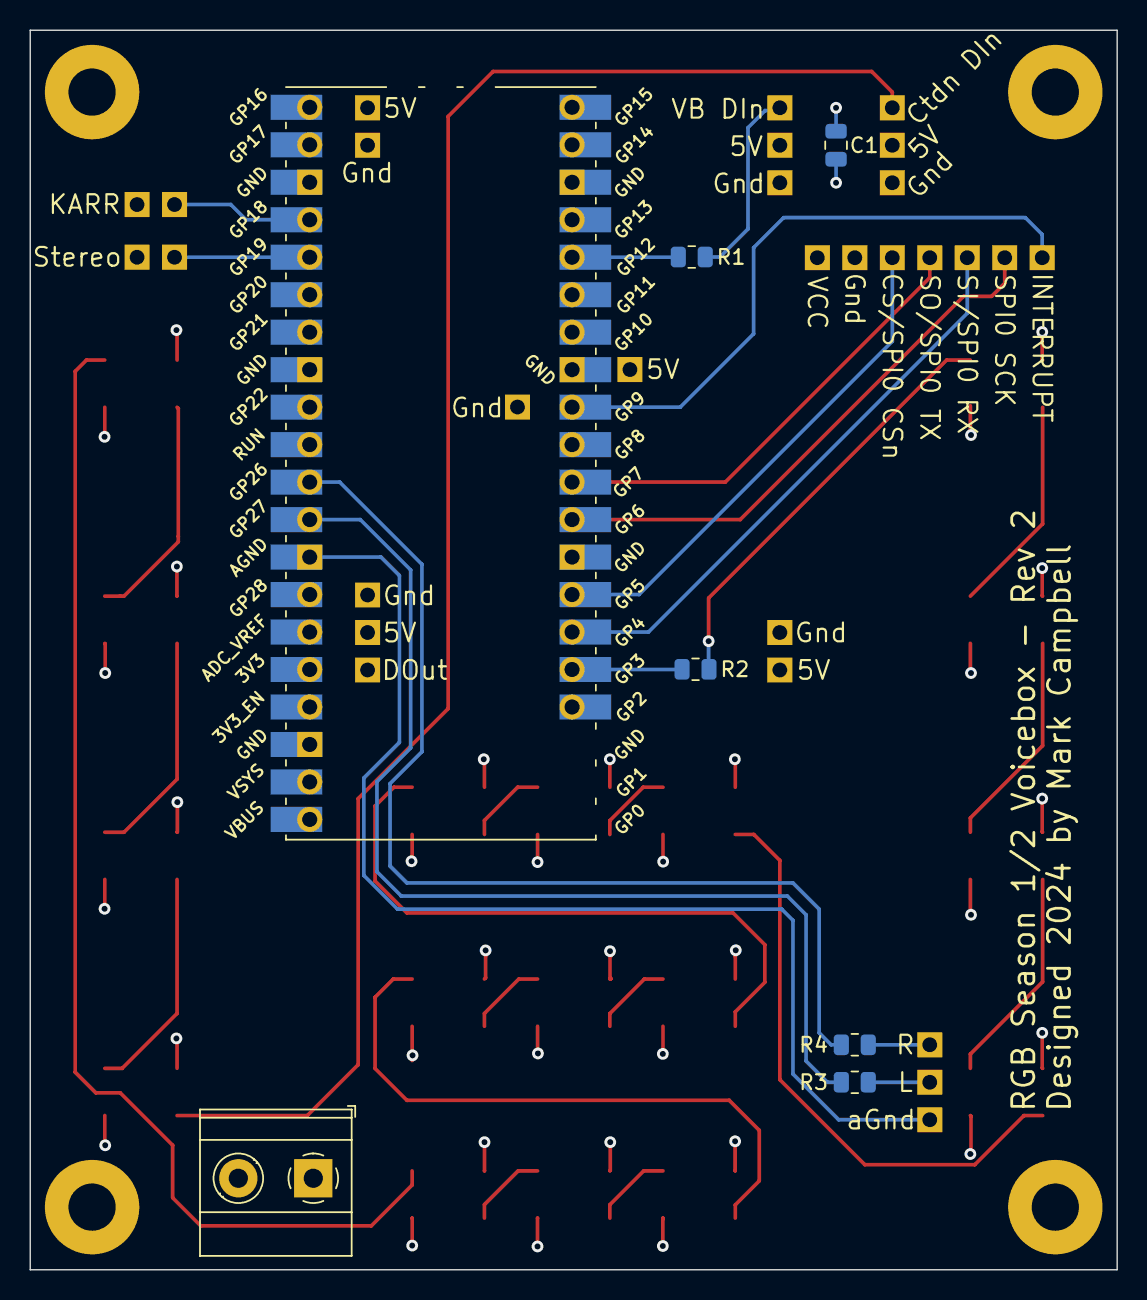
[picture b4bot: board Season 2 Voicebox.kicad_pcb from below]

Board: 4 copper layers, 73.7 x 84.0 mm, 48 parts (13 on the bottom side), 24 nets.

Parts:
5V, 5V#2, 5V#3, 5V#4, 5V#5: (no value)
C1: 1mf; C_0805_2012Metric
CS/SPI0 CSn: (no value)
Ctdn DIn: (no value)
D1, D2, D3, D4, D5, D6, D7, D8, D9, D10, D11, D12, D13, D14, D15, D16, D17: SK6812; LED_SK6812_PLCC4_5.0x5.0mm_P3.2mm
DOut: (no value)
Gnd: (no value)
Gnd#2, Gnd#3, Gnd#4, Gnd#5, Gnd#6, Gnd#7, Gnd#8: (no value)
INTERRUPT: (no value)
KARR: (no value)
R: (no value)
R1, R2, R3, R4: 470; R_0805_2012Metric
SI/SPI0 RX: (no value)
SO/SPI0 TX: (no value)
SPI0 SCK: (no value)
Stereo: (no value)
U1: Pico; RPi_Pico_SMD_TH_Voicebox
VB DIn: (no value)
VCC: (no value)

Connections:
+5V: 5V.1, 5V#2.1, 5V#3.1, 5V#4.1, 5V#5.1, C1.1, D1.3 (VDD), D2.3 (VDD), D3.3 (VDD), D4.3 (VDD), D5.3 (VDD), D6.3 (VDD), D7.3 (VDD), D8.3 (VDD), D9.3 (VDD), D10.3 (VDD), D11.3 (VDD), D12.3 (VDD), D13.3 (VDD), D14.3 (VDD), D15.3 (VDD), D16.3 (VDD), D17.3 (VDD), U1.40 (VBUS), VCC.1
GND: C1.2, D1.1 (VSS), D2.1 (VSS), D3.1 (VSS), D4.1 (VSS), D5.1 (VSS), D6.1 (VSS), D7.1 (VSS), D8.1 (VSS), D9.1 (VSS), D10.1 (VSS), D11.1 (VSS), D12.1 (VSS), D13.1 (VSS), D14.1 (VSS), D15.1 (VSS), D16.1 (VSS), D17.1 (VSS), Gnd.1, Gnd#2.1, Gnd#3.1, Gnd#4.1, Gnd#5.1, Gnd#6.1, Gnd#7.1, Gnd#8.1, U1.8 (GND), U1.13 (GND), U1.18 (GND), U1.23 (GND), U1.28 (GND), U1.38 (GND)
unnamed: D1.2 (DIN), R2.2
unnamed: D1.4 (DOUT), D2.2 (DIN)
unnamed: D2.4 (DOUT), D3.2 (DIN)
unnamed: D3.4 (DOUT), D4.2 (DIN)
unnamed: D4.4 (DOUT), D5.2 (DIN)
unnamed: D5.4 (DOUT), D6.2 (DIN)
unnamed: D6.4 (DOUT), D7.2 (DIN)
unnamed: D7.4 (DOUT), D8.2 (DIN)
unnamed: D8.4 (DOUT), D9.2 (DIN)
unnamed: D9.4 (DOUT), D10.2 (DIN)
unnamed: D10.4 (DOUT), D11.2 (DIN)
unnamed: D11.4 (DOUT), D12.2 (DIN)
unnamed: D12.4 (DOUT), D13.2 (DIN)
unnamed: D13.4 (DOUT), D14.2 (DIN)
unnamed: D14.4 (DOUT), D15.2 (DIN)
unnamed: D15.4 (DOUT), D16.2 (DIN)
unnamed: D16.4 (DOUT), D17.2 (DIN)
unnamed: R.1, R4.2
unnamed: R2.1, U1.5 (GPIO3)
unnamed: R1.2, U1.16 (GPIO12)
unnamed: R4.1, U1.31 (GPIO26_ADC0)
unnamed: R3.1, U1.32 (GPIO27_ADC1)

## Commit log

2020-10-09 Adding projects
    Adding projects for pixie scanner, 2 TV Bezel, and Raspberry Pi computer setup scripts.
2022-03-19 Adding arduino scripts
    Adding arduino scripts for scanner, and shift selector
2022-03-19 Update scanner_NeoPixel_ArduinoMega.ino
    Cleanup of comments
2023-04-12 Update Shifter_selector.ino
    setting more helpful print statements for debug purposes.
2023-04-30 Addition of KITT voice box KiCAD files
2023-11-24 Updates of a number of files
    Updates of a number of files
2024-07-23 Reorganizing projects for better grouping
2024-08-13 Progress on speedo pcb
2024-09-01 Season 1/2 Speedo board updates
    Season 1/2 Speedo board mostly complete, a few modifications still pending.
2024-09-22 7 Segment displays added
    Added 4 layer and 2 layer 7 segment displays designed for the Season 1/2 Speedometer and Tachometer displays
